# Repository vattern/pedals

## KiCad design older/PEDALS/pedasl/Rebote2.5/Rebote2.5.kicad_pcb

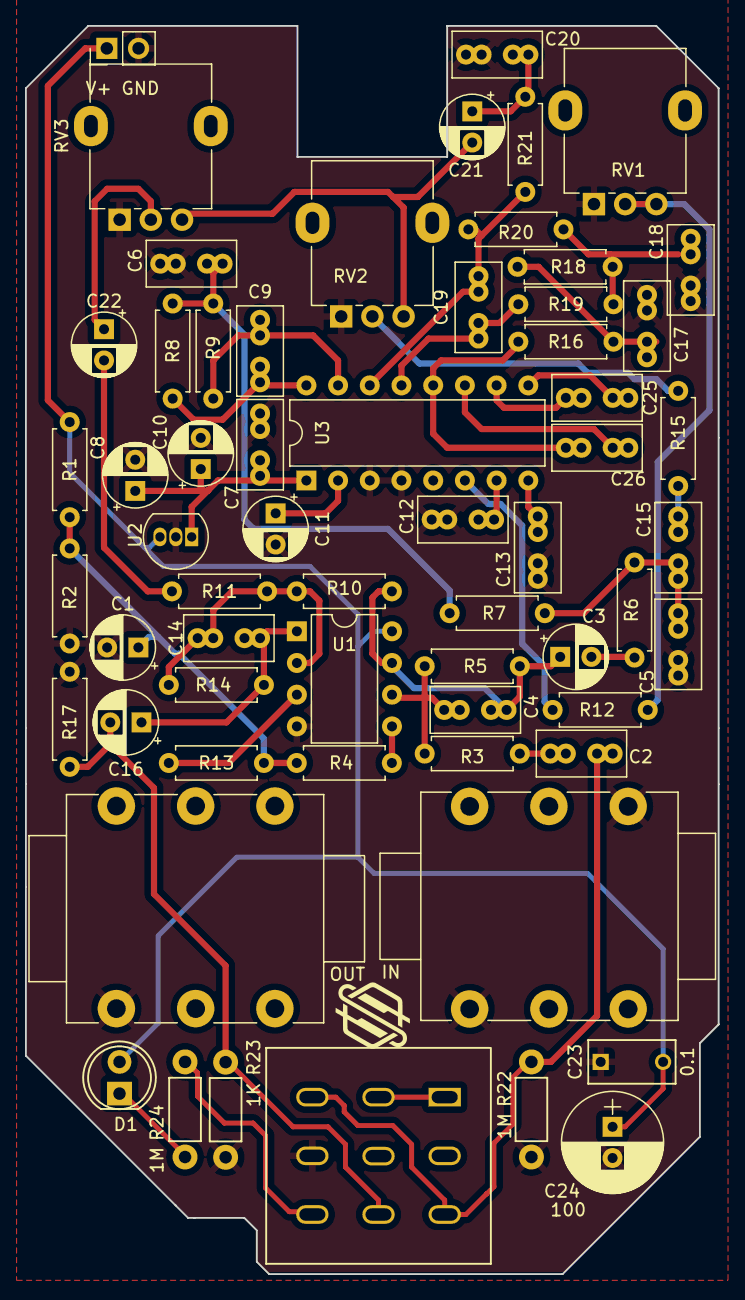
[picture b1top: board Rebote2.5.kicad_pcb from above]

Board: 2 copper layers, 55.5 x 100.0 mm, 62 parts (0 on the bottom side), 40 nets.

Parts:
C1, C8, C10, C11: 47uF; CP_Radial_D5.0mm_P2.50mm
C2: 8n2; C_Rect_L7.0mm_W3.5mm_P2.50mm_P5.00mm
C3, C16, C21, C22: 1uF; CP_Radial_D5.0mm_P2.50mm
C4: 5pF; C_Rect_L7.0mm_W3.5mm_P2.50mm_P5.00mm
C5: 27nF; C_Rect_L7.0mm_W3.5mm_P2.50mm_P5.00mm
C6, C17, C18: 10nF; C_Rect_L7.0mm_W3.5mm_P2.50mm_P5.00mm
C7, C12, C13, C15, C20: 100nF; C_Rect_L7.0mm_W3.5mm_P2.50mm_P5.00mm
C9: 560pF; C_Rect_L7.0mm_W3.5mm_P2.50mm_P5.00mm
C14: 51pF; C_Rect_L7.0mm_W3.5mm_P2.50mm_P5.00mm
C19: 1nF; C_Rect_L7.0mm_W3.5mm_P2.50mm_P5.00mm
C23: 0.1; C_Rect_L7_W3.5_P5
C24: 100; CP_Radial_D8.0mm_P2.50mm
C25, C26: 82nF; C_Rect_L7.0mm_W3.5mm_P2.50mm_P5.00mm
D1: LED; LED-5MM
J1: V+ GND; Pin_Header_Straight_1x02_Pitch2.54mm
J2: IN; NMJ6HCD2
J3: OUT; NMJ6HCD2
N1: Housing; 1590B
R1, R2, R6, R7, R8, R16, R18, R19: 12K; R_Axial_DIN0207_L6.3mm_D2.5mm_P7.62mm_Horizontal
R3, R4, R5: 510K; R_Axial_DIN0207_L6.3mm_D2.5mm_P7.62mm_Horizontal
R9: 47K; R_Axial_DIN0207_L6.3mm_D2.5mm_P7.62mm_Horizontal
R10, R14, R20: 24K; R_Axial_DIN0207_L6.3mm_D2.5mm_P7.62mm_Horizontal
R11: 33K; R_Axial_DIN0207_L6.3mm_D2.5mm_P7.62mm_Horizontal
R12, R13: 1k; R_Axial_DIN0207_L6.3mm_D2.5mm_P7.62mm_Horizontal
R15: 15K; R_Axial_DIN0207_L6.3mm_D2.5mm_P7.62mm_Horizontal
R17: 100K; R_Axial_DIN0207_L6.3mm_D2.5mm_P7.62mm_Horizontal
R21: 2k7; R_Axial_DIN0207_L6.3mm_D2.5mm_P7.62mm_Horizontal
R22, R24: 1M; Resistor_Horizontal_RM7mm
R23: 1K; Resistor_Horizontal_RM7mm
RV1: 50KB; Potentiometer_Alpha_RD901F-40-00D_Single_Vertical
RV2: 25KB; Potentiometer_Alpha_RD901F-40-00D_Single_Vertical
RV3: 100KB; Potentiometer_Alpha_RD901F-40-00D_Single_Vertical
SW1: SW_3PDT; 3PDT-Footswitch
U1: TL072; DIP-8_W7.62mm
U2: L78L05_TO92; TO-92_Inline
U3: PT2399; DIP-16_W7.62mm

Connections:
+5V: C7.2, C8.1, C10.1, U2.1 (VO), U3.1 (VCC)
+9V: C23.2, C24.1, D1.2 (A), J1.1, R1.1, U1.8 (V+), U2.3 (VI)
AI: C3.1, C4.2, R5.2, R10.1, U1.7
DELAY_OUT: C26.2, R16.1, U3.12 (OP2-OUT)
GND: C1.2, C5.1, C6.1, C7.1, C8.2, C10.2, C11.2, C12.1, C13.1, C17.1, C18.1, C20.1, C23.1, C24.2, J1.2, J2.1 (S), J2.5 (TN), J3.1 (S), R2.2, R17.1, R22.2, R23.2, RV1.1, RV2.1, RV3.1, SW1.6 (B), U1.4 (V-), U2.2 (GND), U3.3 (AGND), U3.4 (DGND)
I: C2.1, R22.1, SW1.3 (A), SW1.7 (C)
LPF1-IN: C9.1, R8.2, U3.16 (LPF1-IN)
LPF1-OUT: C9.2, R9.2, U3.15 (LPF1-OUT)
LPF2-IN: C19.1, R19.2, U3.13 (LPF2-IN)
LPF2-OUT: C19.2, R20.2, R21.1, U3.14 (LPF2-OUT)
unnamed: C2.2, R3.1
unnamed: C3.2, R6.1
unnamed: C6.2, R7.2, R8.1, R9.1
unnamed: C14.2, C16.1, R14.2, U1.1
unnamed: C5.2, C15.1, R6.2, R7.1
unnamed: C15.2, R15.1
unnamed: C17.2, R16.2, R18.1
unnamed: C18.2, R18.2, R19.1, R20.1
unnamed: C20.2, C21.1, R21.2
unnamed: C21.2, RV2.3, RV3.3
unnamed: C22.1, RV3.2
unnamed: C22.2, R11.1
unnamed: D1.1 (K), R24.1
unnamed: R12.2, RV1.2, RV1.3
unnamed: R15.2, RV2.2
unnamed: SW1.1 (A), SW1.2 (A)
unnamed: R24.2, SW1.9 (C)
unnamed: R13.2, U1.3 (+)
unnamed: C14.1, R10.2, R11.2, R14.1, U1.2 (-)
unnamed: R4.2, U1.5 (+)
unnamed: C4.1, R3.2, R5.1, U1.6 (-)
unnamed: C13.2, U3.8 (CC0)
unnamed: C12.2, U3.7 (CC1)
unnamed: C25.2, U3.10 (OP1-IN)
unnamed: C25.1, U3.9 (OP1-OUT)
unnamed: C26.1, U3.11 (OP2-IN)
unnamed: C11.1, U3.2 (REF)
unnamed: R12.1, U3.6 (VCO)
O: C16.2, R17.2, R23.1, SW1.8 (C)
VD: C1.1, R1.2, R2.1, R4.1, R13.1

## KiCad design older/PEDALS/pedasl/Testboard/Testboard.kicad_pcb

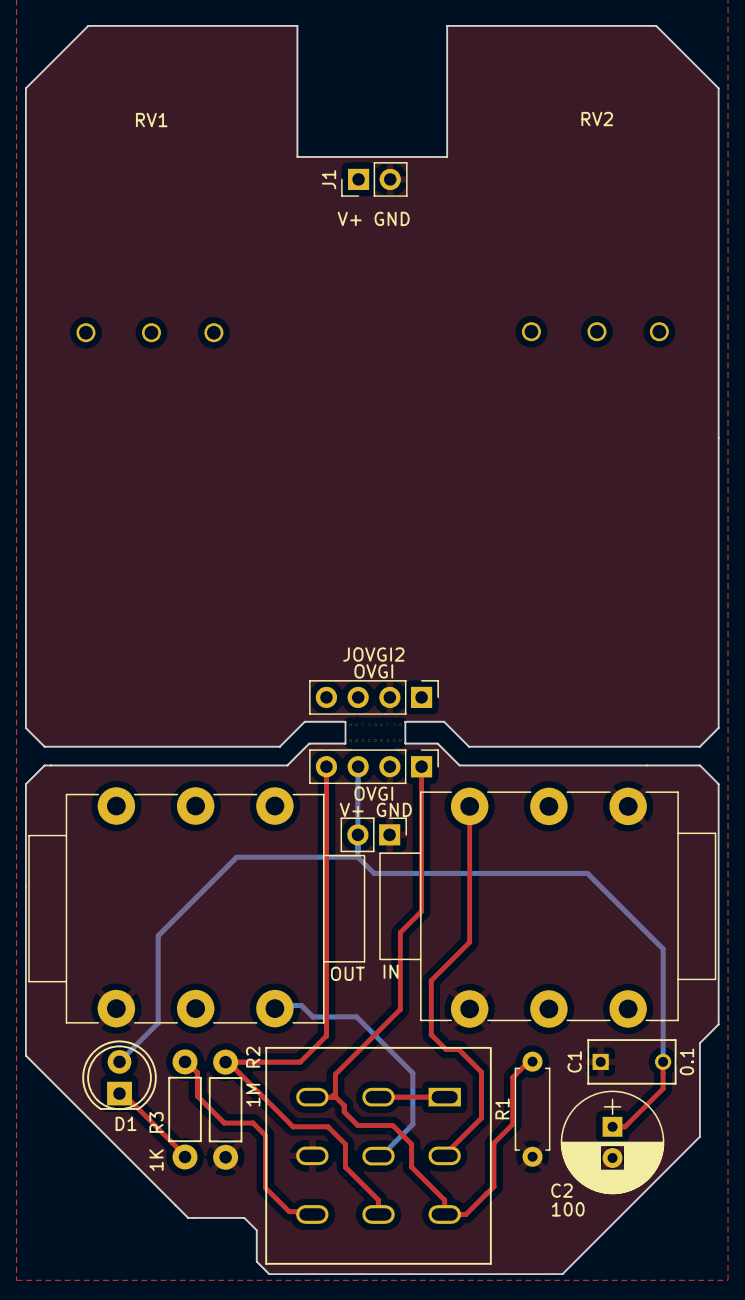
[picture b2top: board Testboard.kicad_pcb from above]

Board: 2 copper layers, 55.5 x 100.0 mm, 15 parts (0 on the bottom side), 9 nets.

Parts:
C1: 0.1; C_Rect_L7_W3.5_P5
C2: 100; CP_Radial_D8.0mm_P2.50mm
D1: LED; LED-5MM
J1, J4: V+ GND; Pin_Header_Straight_1x02_Pitch2.54mm
J2: IN; NMJ6HCD2
J3: OUT; NMJ6HCD2
JOVGI1, JOVGI2: OVGI; Pin_Header_Straight_1x04_Pitch2.54mm
R1: R; R_Axial_DIN0207_L6.3mm_D2.5mm_P7.62mm_Horizontal
R2: 1M; Resistor_Horizontal_RM7mm
R3: 1K; Resistor_Horizontal_RM7mm
RV1, RV2: R_Potentiometer; Potentiometer_ALPHA_RV16106N
SW1: SW_3PDT; 3PDT-Footswitch

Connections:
+9V: C1.2, C2.1, D1.2, J1.1, J4.2, JOVGI1.3, JOVGI2.3
/I: JOVGI1.1, JOVGI2.1, SW1.3, SW1.7
/O: JOVGI1.4, JOVGI2.4, R2.1, SW1.8
GND: C1.1, C2.2, J1.2, J2.1, J2.5, J3.1, J4.1, JOVGI1.2, JOVGI2.2, R1.1, R2.2, SW1.6
unnamed: D1.1, R3.1
unnamed: J2.2, SW1.4
unnamed: J3.2, SW1.5
unnamed: R3.2, SW1.9
unnamed: SW1.1, SW1.2

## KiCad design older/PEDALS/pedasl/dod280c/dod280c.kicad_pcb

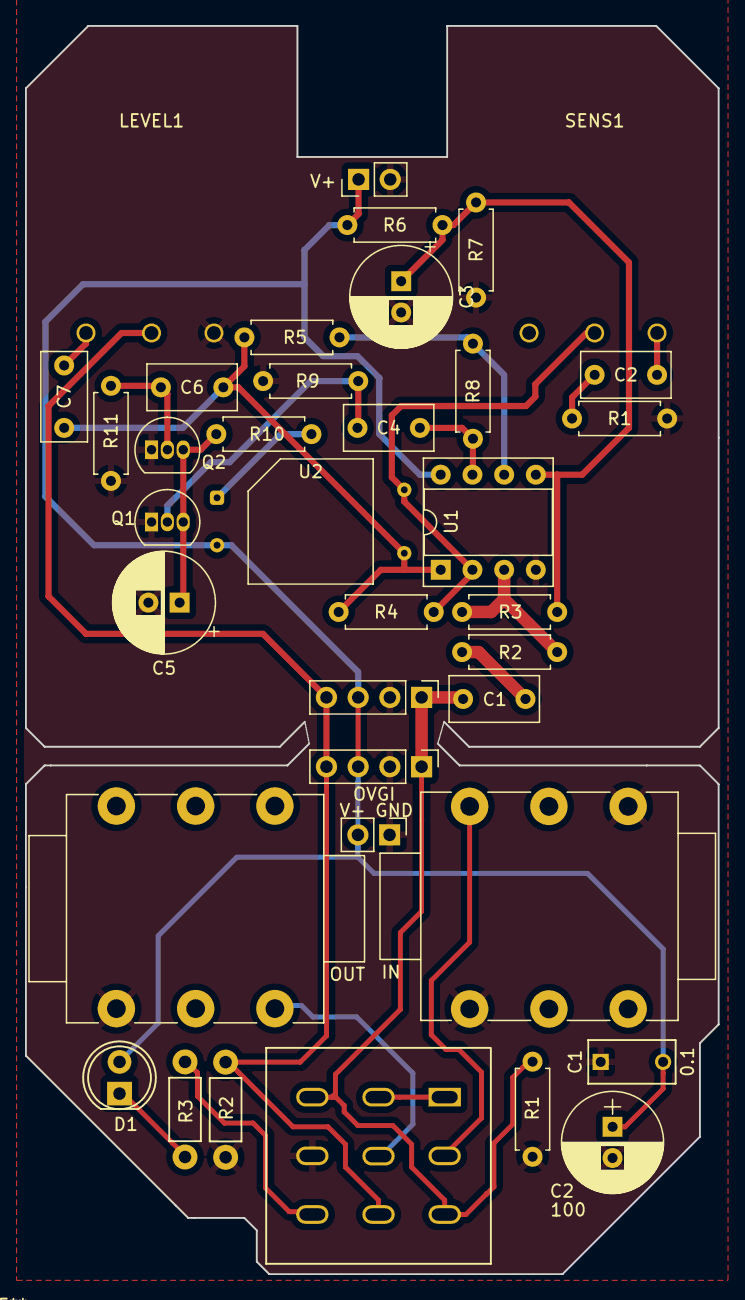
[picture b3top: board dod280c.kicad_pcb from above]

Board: 2 copper layers, 55.5 x 100.0 mm, 37 parts (0 on the bottom side), 23 nets.

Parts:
C1: 10nF; C_Rect_L7.0mm_W3.5mm_P5.00mm
C1#2: 0.1; C_Rect_L7_W3.5_P5
C2, C4, C6, C7: 50nF; C_Rect_L7.0mm_W3.5mm_P5.00mm
C2#2: 100; CP_Radial_D8.0mm_P2.50mm
C3: 10uF; CP_Radial_D8.0mm_P2.50mm
C5: 47uF; CP_Radial_D8.0mm_P2.50mm
D1: LED; LED-5MM
J1: V+; Pin_Header_Straight_1x02_Pitch2.54mm
J2: IN; NMJ6HCD2
J3: OUT; NMJ6HCD2
J4: V+ GND; Pin_Header_Straight_1x02_Pitch2.54mm
JOVGI1, JOVGI2: OVGI; Pin_Header_Straight_1x04_Pitch2.54mm
LEVEL1: 100KA; Potentiometer_ALPHA_RV16106N
Q1, Q2: 2N3904; TO-92_Inline
R1: R; R_Axial_DIN0207_L6.3mm_D2.5mm_P7.62mm_Horizontal
R1#2, R6, R7: 22K; R_Axial_DIN0207_L6.3mm_D2.5mm_P7.62mm_Horizontal
R2: 1M; Resistor_Horizontal_RM7mm
R2#2: 10K; R_Axial_DIN0207_L6.3mm_D2.5mm_P7.62mm_Horizontal
R3: 1K; Resistor_Horizontal_RM7mm
R3#2: 470K; R_Axial_DIN0207_L6.3mm_D2.5mm_P7.62mm_Horizontal
R4: 1M; R_Axial_DIN0207_L6.3mm_D2.5mm_P7.62mm_Horizontal
R5, R8: 100K; R_Axial_DIN0207_L6.3mm_D2.5mm_P7.62mm_Horizontal
R9, R11: 220K; R_Axial_DIN0207_L6.3mm_D2.5mm_P7.62mm_Horizontal
R10: 4K7; R_Axial_DIN0207_L6.3mm_D2.5mm_P7.62mm_Horizontal
SENS1: 500KB; Potentiometer_ALPHA_RV16106N
SW1: SW_3PDT; 3PDT-Footswitch
U1: LM358; DIP-8_W7.62mm_Socket
U2: VTL5C; PerkinElmer_VTL5C

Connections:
+9V: C1#2.2, C2#2.1, D1.2, J1.1, J4.2, JOVGI1.3, JOVGI2.3, R6.1, U1.8 (V+), U2.2 (+)
GND: C1#2.1, C2#2.2, C3.2, C5.2, J1.2, J2.1, J2.5, J3.1, J4.1, JOVGI1.2, JOVGI2.2, LEVEL1.3, Q1.1 (E), Q2.1 (E), R1.1, R1#2.2, R2.2, R7.2, R9.2, R11.2, SW1.6, U1.4 (V-)
unnamed: C1.2, R2#2.1
unnamed: C2.1, R1#2.1
unnamed: C2.2, SENS1.3
unnamed: C4.1, R8.2, U1.7
unnamed: C6.2, C7.1, R4.2, R5.1, U1.1, U2.4
unnamed: C7.2, LEVEL1.1
unnamed: D1.1, R3.1
unnamed: J2.2, SW1.4
unnamed: J3.2, SW1.5
unnamed: C4.2, Q1.2 (B), R9.1
unnamed: C5.1, Q1.3 (C), Q2.3 (C), R10.2
unnamed: C6.1, Q2.2 (B), R11.1
unnamed: R3.2, SW1.9
unnamed: SW1.1, SW1.2
unnamed: R2#2.2, R3#2.2, U1.3 (+)
unnamed: R4.1, SENS1.2, U1.2 (-), U2.3
unnamed: R5.2, R8.1, U1.6 (-)
unnamed: R10.1, U2.1 (-)
VB: C3.1, R3#2.1, R6.2, R7.1, U1.5 (+)
/I: C1.1, JOVGI1.1, JOVGI2.1, R1.2, SW1.3, SW1.7
/O: JOVGI1.4, JOVGI2.4, LEVEL1.2, R2.1, SW1.8

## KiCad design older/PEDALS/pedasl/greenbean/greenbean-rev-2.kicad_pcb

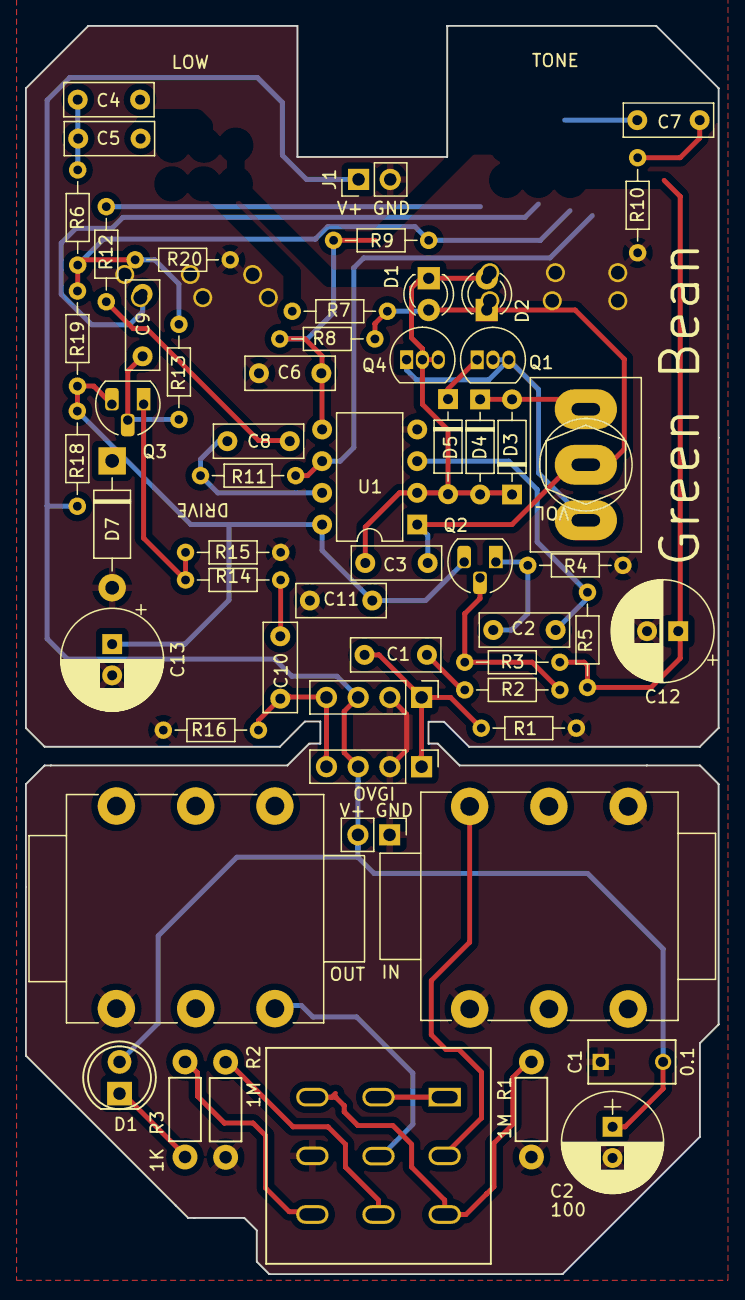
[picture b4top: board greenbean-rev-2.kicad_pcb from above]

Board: 2 copper layers, 55.5 x 100.0 mm, 61 parts (0 on the bottom side), 36 nets.

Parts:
C1: 0.1; C_Rect_L7_W3.5_P5
C1#2: 20n; C_Disc_D7.0mm_W2.5mm_P5.00mm
C2, C8, C10: 1u; C_Disc_D7.0mm_W2.5mm_P5.00mm
C2#2: 100; CP_Radial_D8.0mm_P2.50mm
C3: 51p; C_Disc_D7.0mm_W2.5mm_P5.00mm
C4: 47n; C_Disc_D7.0mm_W2.5mm_P5.00mm
C5: 150n; C_Disc_D7.0mm_W2.5mm_P5.00mm
C6, C7, C11: 220n; C_Disc_D7.0mm_W2.5mm_P5.00mm
C9: 100n; C_Disc_D7.0mm_W2.5mm_P5.00mm
C12, C13: C_Polarized; CP_Radial_D8.0mm_P2.50mm
D1, D2: LED; LED_D3.0mm
D1#2: LED; LED-5MM
D3, D4: 1N914; D_DO-35_SOD27_P7.62mm_Horizontal
D5: BAT41; D_DO-35_SOD27_P7.62mm_Horizontal
D7: 1N4001; D_DO-41_SOD81_P10.16mm_Horizontal
DRIVE: 500KA; Potentiometer_ALPHA_RV16106N
J1, J4: V+ GND; Pin_Header_Straight_1x02_Pitch2.54mm
J2: IN; NMJ6HCD2
J3: OUT; NMJ6HCD2
JOVGI1, JOVGI2: OVGI; Pin_Header_Straight_1x04_Pitch2.54mm
LOW: 20KB; Potentiometer_ALPHA_RV16106N
Q1, Q4: 2N7000; TO-92_Inline
Q2, Q3: Q_NPN_EBC; TO-92L_HandSolder
R1: 1M; R_Axial_DIN0204_L3.6mm_D1.6mm_P7.62mm_Horizontal
R1#2, R2#2: 1M; Resistor_Horizontal_RM7mm
R2, R8, R11, R12: 1k; R_Axial_DIN0204_L3.6mm_D1.6mm_P7.62mm_Horizontal
R3, R13: 510k; R_Axial_DIN0204_L3.6mm_D1.6mm_P7.62mm_Horizontal
R3#2: 1K; Resistor_Horizontal_RM7mm
R4, R5, R9, R14, R16, R19, R20: 10k; R_Axial_DIN0204_L3.6mm_D1.6mm_P7.62mm_Horizontal
R6: 4k7; R_Axial_DIN0204_L3.6mm_D1.6mm_P7.62mm_Horizontal
R7: 51k; R_Axial_DIN0204_L3.6mm_D1.6mm_P7.62mm_Horizontal
R10: 220R; R_Axial_DIN0204_L3.6mm_D1.6mm_P7.62mm_Horizontal
R15: 100R; R_Axial_DIN0204_L3.6mm_D1.6mm_P7.62mm_Horizontal
R18: 47R; R_Axial_DIN0204_L3.6mm_D1.6mm_P7.62mm_Horizontal
SW1: SW_3PDT; 3PDT-Footswitch
SW1#2: SW_SPDT; SW_Toggle_Blue_wSlots
TONE: 20KB; Potentiometer_ALPHA_RV16106N
U1: RC4558; DIP-8_W7.62mm
VOL: 100KB; Potentiometer_ALPHA_RV16106N

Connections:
+9V: C1.2, C2#2.1, D1#2.2, J1.1, J4.2, JOVGI1.3, JOVGI2.3, R18.2
/I: R1#2.1, SW1.3, SW1.7
/O: R2#2.1, SW1.8
A: C3.1, C4.2, D1.1 (K), D2.2 (A), D3.1 (K), D4.2 (A), D5.2 (A), DRIVE.1, LOW.3, Q4.2 (G), Q4.3 (D), U1.2 (-)
B: C3.2, D1.2 (A), D2.1 (K), R7.2, R8.1, SW1#2.2 (B), U1.1
GND: C1.1, C2#2.2, C6.1, C11.1, C12.2, C13.2, D7.2 (A), J1.2, J2.1, J2.5, J3.1, J4.1, JOVGI1.2, JOVGI2.2, R1.1, R1#2.2, R2#2.2, R4.1, R10.1, R14.1, R16.1, R20.1, SW1.6, U1.4 (V-)
unnamed: C1#2.2, R2.2
unnamed: C4.1, C5.1, R6.2
unnamed: C5.2, LOW.2
unnamed: C7.1, R10.2
unnamed: C7.2, TONE.2
unnamed: C8.1, R11.2, U1.7
unnamed: C8.2, R12.1
unnamed: C9.1, VOL.2
unnamed: C10.1, R15.2
unnamed: D1#2.1, R3#2.1
unnamed: D3.2 (A), D4.1 (K), SW1#2.1 (A)
unnamed: D5.1 (K), Q1.1 (S)
unnamed: DRIVE.2, DRIVE.3, R7.1
unnamed: J2.2, SW1.4
unnamed: J3.2, SW1.5
unnamed: Q1.2 (G), Q1.3 (D), Q4.1 (S), SW1#2.3 (C)
unnamed: Q2.2 (B), R2.1, R3.1
unnamed: C2.1, Q2.1 (E), R4.2
unnamed: C9.2, Q3.2 (B), R13.1
unnamed: Q3.1 (E), R14.2, R15.1
unnamed: R3#2.2, SW1.9
unnamed: R12.2, VOL.3
unnamed: SW1.1, SW1.2
unnamed: C2.2, R5.1, U1.3 (+)
unnamed: C6.2, R8.2, R9.1, TONE.1, U1.5 (+)
unnamed: R11.1, TONE.3, U1.6 (-)
VB: C12.1, R3.2, R5.2, R6.1, R9.2, R13.2, R19.1, R20.2, VOL.1
VC: C11.2, C13.1, D7.1 (K), Q2.3 (C), Q3.3 (C), R18.1, R19.2, U1.8 (V+)
/I: C1#2.1, JOVGI1.1, JOVGI2.1, R1.2
/O: C10.2, JOVGI1.4, JOVGI2.4, R16.2

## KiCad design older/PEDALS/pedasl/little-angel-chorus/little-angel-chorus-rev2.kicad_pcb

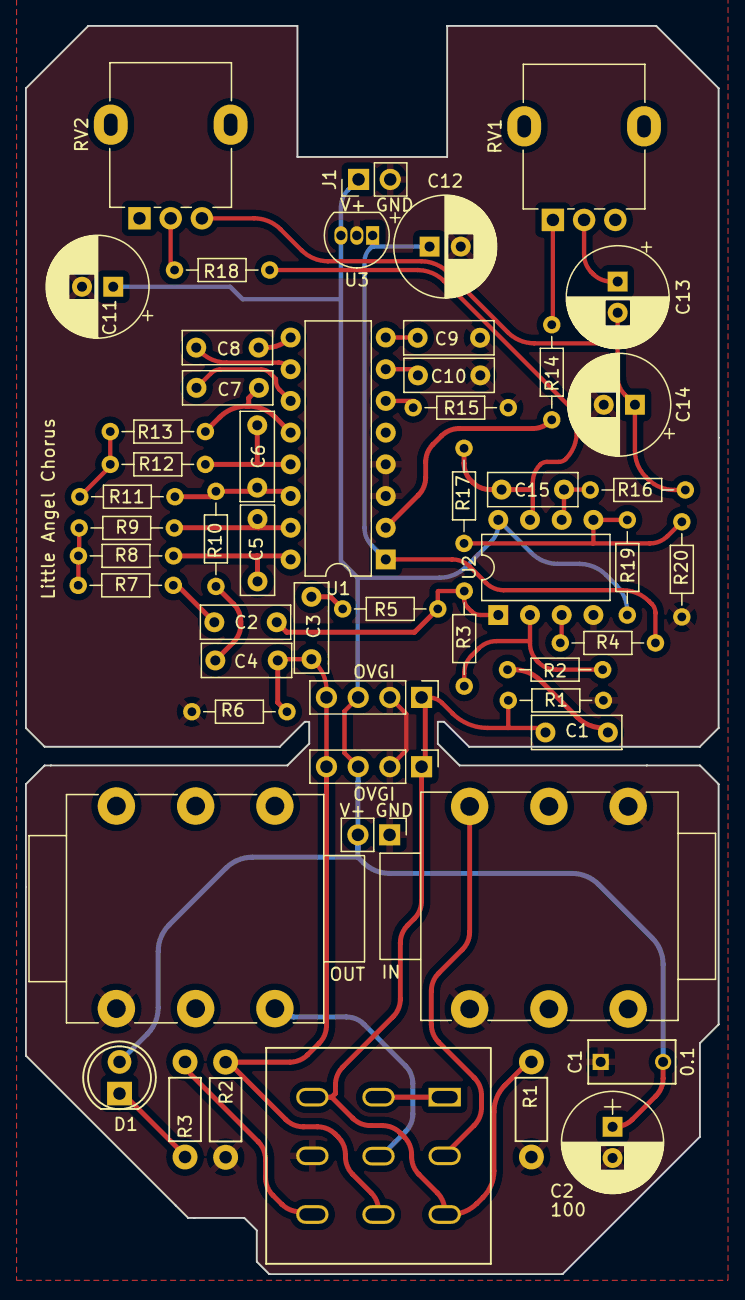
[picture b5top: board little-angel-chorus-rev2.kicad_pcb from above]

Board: 2 copper layers, 55.5 x 100.0 mm, 53 parts (0 on the bottom side), 38 nets.

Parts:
C1: 0.1; C_Rect_L7_W3.5_P5
C1#2, C2, C3, C4, C9, C10: 100nF; C_Disc_D7.0mm_W2.5mm_P5.00mm
C2#2: 100; CP_Radial_D8.0mm_P2.50mm
C5, C6: 1nF; C_Disc_D7.0mm_W2.5mm_P5.00mm
C7, C8, C15: 10nF; C_Disc_D7.0mm_W2.5mm_P5.00mm
C11: 100uF; CP_Radial_D8.0mm_P2.50mm
C12: 47uF; CP_Radial_D8.0mm_P2.50mm
C13, C14: 10uF; CP_Radial_D8.0mm_P2.50mm
D1: LED; LED-5MM
J1, J4: V+ GND; Pin_Header_Straight_1x02_Pitch2.54mm
J2: IN; NMJ6HCD2
J3: OUT; NMJ6HCD2
JOVGI1, JOVGI2: OVGI; Pin_Header_Straight_1x04_Pitch2.54mm
R1, R2: 1M; Resistor_Horizontal_RM7mm
R1#2, R3: 1M; R_Axial_DIN0204_L3.6mm_D1.6mm_P7.62mm_Horizontal
R2#2: 470k; R_Axial_DIN0204_L3.6mm_D1.6mm_P7.62mm_Horizontal
R3#2: 1K; Resistor_Horizontal_RM7mm
R4: 330k; R_Axial_DIN0204_L3.6mm_D1.6mm_P7.62mm_Horizontal
R5, R7, R8, R9, R10, R11, R12, R13: 10k; R_Axial_DIN0204_L3.6mm_D1.6mm_P7.62mm_Horizontal
R6, R19: 100k; R_Axial_DIN0204_L3.6mm_D1.6mm_P7.62mm_Horizontal
R14: 33k; R_Axial_DIN0204_L3.6mm_D1.6mm_P7.62mm_Horizontal
R15: 100R; R_Axial_DIN0204_L3.6mm_D1.6mm_P7.62mm_Horizontal
R16: 220K; R_Axial_DIN0204_L3.6mm_D1.6mm_P7.62mm_Horizontal
R17: 220k; R_Axial_DIN0204_L3.6mm_D1.6mm_P7.62mm_Horizontal
R18: 4k7; R_Axial_DIN0204_L3.6mm_D1.6mm_P7.62mm_Horizontal
R20: 47k; R_Axial_DIN0204_L3.6mm_D1.6mm_P7.62mm_Horizontal
RV1: 470K lin; Potentiometer_Alpha_RD901F-40-00D_Single_Vertical
RV2: 100k lin; Potentiometer_Alpha_RD901F-40-00D_Single_Vertical
SW1: SW_3PDT; 3PDT-Footswitch
U1: PT2399; DIP-16_W7.62mm
U2: NE5532; DIP-8_W7.62mm
U3: L78L05_TO92; TO-92_Inline

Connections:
+9V: C1.2, C2#2.1, C11.1, D1.2, J1.1, J4.2, JOVGI1.3, JOVGI2.3, R19.2, U2.8 (V+), U3.3 (VI)
GND: C1.1, C2#2.2, C9.1, C10.1, C11.2, C12.2, C14.2, J1.2, J2.1, J2.5, J3.1, J4.1, JOVGI1.2, JOVGI2.2, R1.2, R1#2.2, R2.2, R6.1, R15.1, R20.1, SW1.6, U1.3 (AGND), U1.4 (DGND), U2.4 (V-), U3.2 (GND)
unnamed: C1#2.2, R2#2.1
unnamed: C2.1, R7.1
unnamed: C2.2, R3.2, R5.1, U2.1
unnamed: C3.1, R5.2
unnamed: C4.1, R10.2
unnamed: C13.1, RV1.2
unnamed: C13.2, C14.1, R16.2, RV2.3
unnamed: C15.2, R17.2, R18.1, U2.7
unnamed: D1.1, R3#2.1
unnamed: J2.2, SW1.4
unnamed: J3.2, SW1.5
unnamed: R3#2.2, SW1.9
unnamed: R7.2, R8.2, R9.2
unnamed: R11.1, R12.1, R13.1
unnamed: R14.1, RV1.1
unnamed: R18.2, RV2.2
unnamed: SW1.1, SW1.2
unnamed: C9.2, U1.8 (CC0)
unnamed: C10.2, U1.7 (CC1)
unnamed: C5.1, R8.1, U1.16 (LPF1-IN)
unnamed: C5.2, R9.1, U1.15 (LPF1-OUT)
unnamed: C6.2, R12.2, U1.13 (LPF2-IN)
unnamed: C6.1, R10.1, R11.2, U1.14 (LPF2-OUT)
unnamed: C8.1, U1.10 (OP1-IN)
unnamed: C8.2, U1.9 (OP1-OUT)
unnamed: C7.2, U1.11 (OP2-IN)
unnamed: C7.1, R13.2, U1.12 (OP2-OUT)
unnamed: R14.2, U1.2 (REF)
unnamed: C12.1, R4.1, U1.1 (VCC), U3.1 (VO)
unnamed: R15.2, U1.6 (VCO)
unnamed: R4.2, U2.3 (+)
unnamed: R2#2.2, R3.1, U2.2 (-)
unnamed: R17.1, R19.1, R20.2, U2.5 (+)
unnamed: C15.1, R16.1, U2.6 (-)
/I: C1#2.1, JOVGI1.1, JOVGI2.1, R1.1, R1#2.1, SW1.3, SW1.7
/O: C3.2, C4.2, JOVGI1.4, JOVGI2.4, R2.1, R6.2, SW1.8

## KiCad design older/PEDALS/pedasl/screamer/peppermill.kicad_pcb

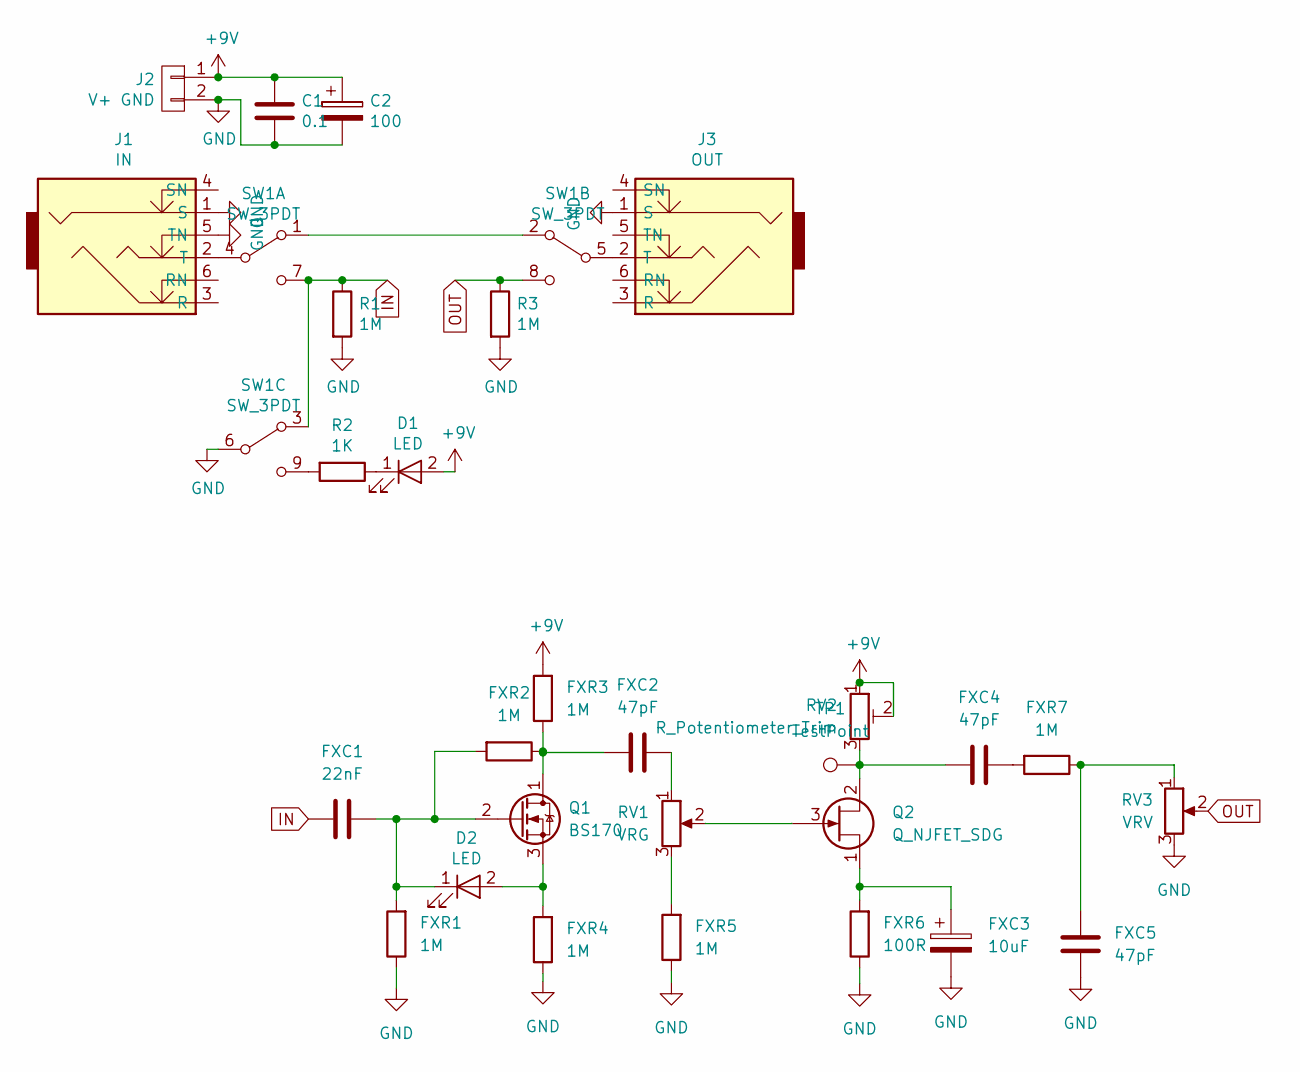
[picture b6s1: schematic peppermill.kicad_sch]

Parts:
C1: 0.1; C_Rect_L7_W3.5_P5
C2: 100; CP_Radial_D8.0mm_P2.50mm
D1: LED; LED-5MM
D2: LED; LED_D5.0mm
FXC1: 22nF; C_Disc_D5.0mm_W2.5mm_P5.00mm
FXC2, FXC4, FXC5: 47pF; C_Disc_D5.0mm_W2.5mm_P5.00mm
FXC3: 10uF; CP_Radial_D7.5mm_P2.50mm
FXR1, FXR2, FXR3, FXR4, FXR5, FXR7: 1M; R_Axial_DIN0207_L6.3mm_D2.5mm_P7.62mm_Horizontal
FXR6: 100R; R_Axial_DIN0207_L6.3mm_D2.5mm_P7.62mm_Horizontal
J1: IN; NMJ6HCD2
J2: V+ GND; Pin_Header_Straight_1x02_Pitch2.54mm
J3: OUT; NMJ6HCD2
Q1: BS170; TO-92_Inline
Q2: Q_NJFET_SDG; TO-92L_Inline_Wide
R1, R3: 1M; Resistor_Horizontal_RM7mm
R2: 1K; Resistor_Horizontal_RM7mm
RV1: VRG; Potentiometer_Alps_RK09K_Single_Vertical
RV2: R_Potentiometer_Trim; Potentiometer_TT_P0915N
RV3: VRV; Potentiometer_Alps_RK09K_Single_Vertical
SW1: SW_3PDT; 3PDT-Footswitch
TP1: TestPoint; TestPoint_Loop_D2.50mm_Drill1.85mm

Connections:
+9V: C1.2, C2.1, D1.2 (A), FXR3.2, J2.1, RV2.1, RV2.2
GND: C1.1, C2.2, FXC3.2, FXC5.1, FXR1.1, FXR4.1, FXR5.1, FXR6.1, J1.1 (S), J1.5 (TN), J2.2, J3.1 (S), R1.2, R3.2, RV3.3, SW1.6 (B)
IN: FXC1.1, R1.1, SW1.3 (A), SW1.7 (C)
unnamed: D1.1 (K), R2.1
unnamed: D2.1 (K), FXC1.2, FXR1.2, FXR2.2, Q1.2 (G)
unnamed: D2.2 (A), FXR4.2, Q1.3 (S)
unnamed: FXC2.1, FXR2.1, FXR3.1, Q1.1 (D)
unnamed: FXC2.2, RV1.1
unnamed: FXC3.1, FXR6.2, Q2.1 (S)
unnamed: FXC4.1, Q2.2 (D), RV2.3, TP1.1
unnamed: FXC4.2, FXR7.2
unnamed: FXC5.2, FXR7.1, RV3.1
unnamed: FXR5.2, RV1.3
unnamed: J1.2 (T), SW1.4 (B)
unnamed: J3.2 (T), SW1.5 (B)
unnamed: Q2.3 (G), RV1.2
unnamed: R2.2, SW1.9 (C)
unnamed: SW1.1 (A), SW1.2 (A)
OUT: R3.1, RV3.2, SW1.8 (C)

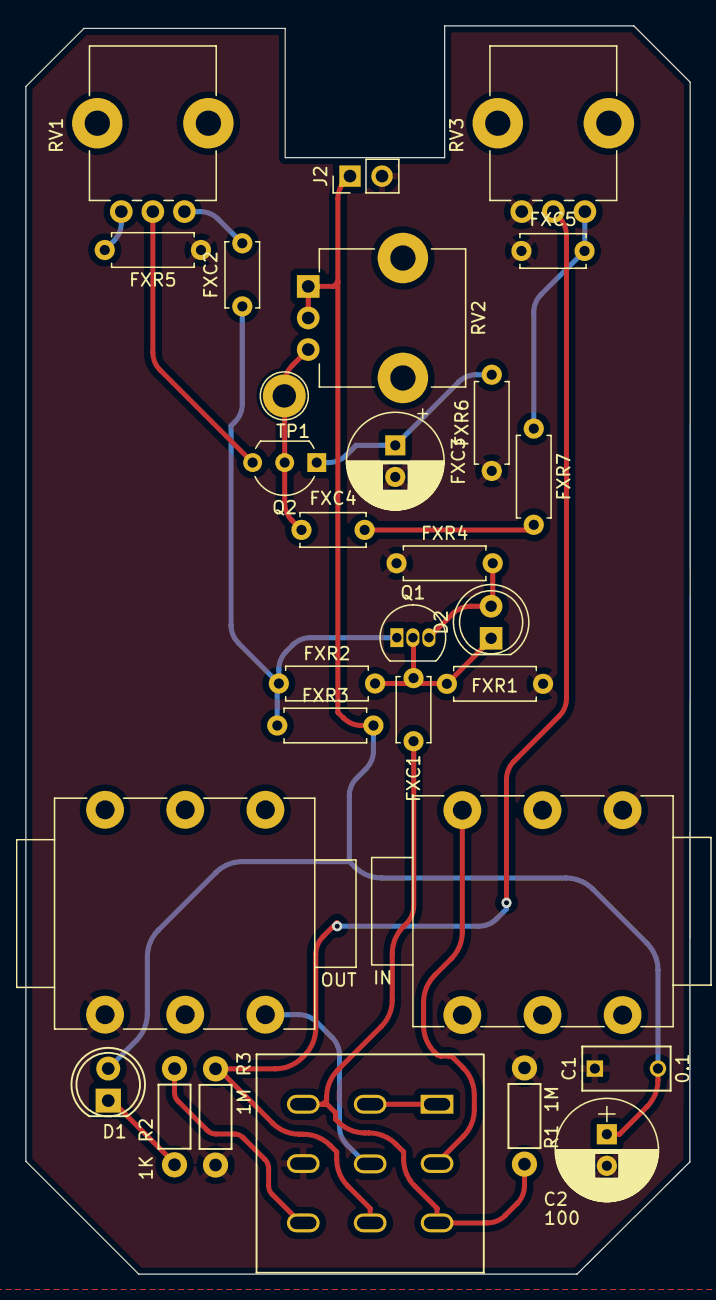
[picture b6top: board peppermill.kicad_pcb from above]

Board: 2 copper layers, 52.6 x 98.9 mm, 29 parts (0 on the bottom side), 19 nets.

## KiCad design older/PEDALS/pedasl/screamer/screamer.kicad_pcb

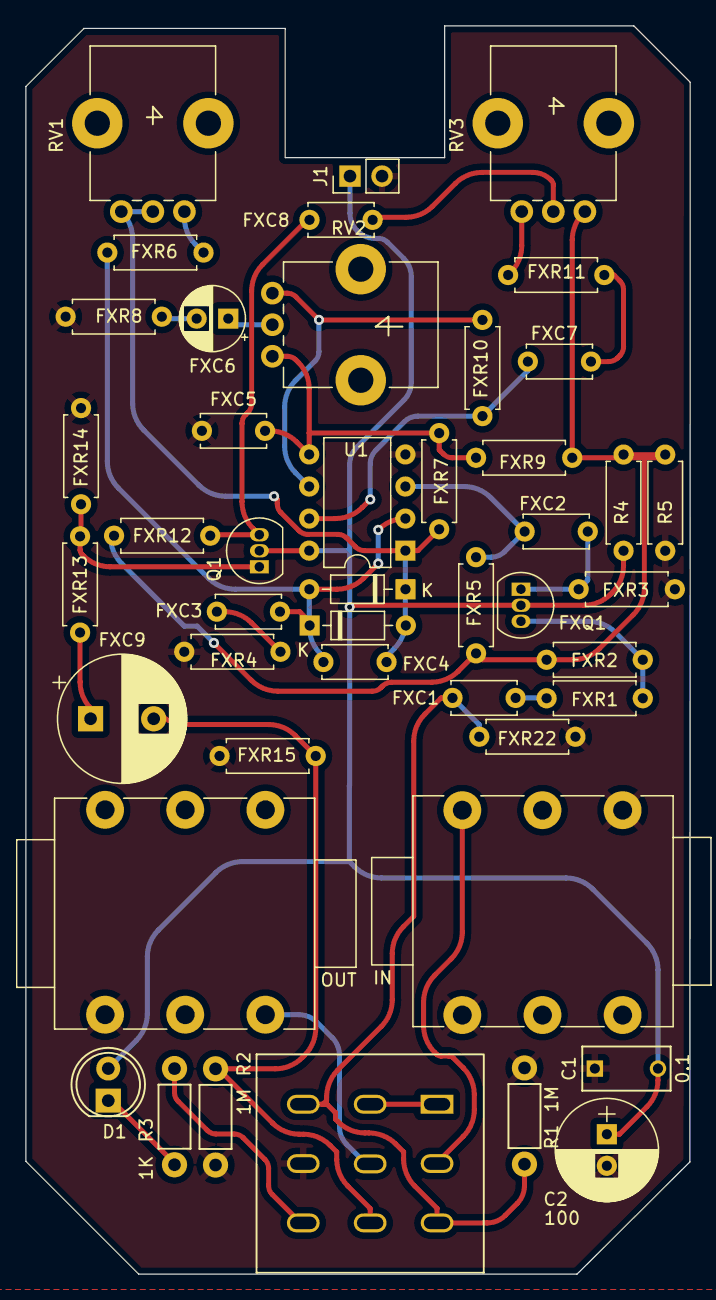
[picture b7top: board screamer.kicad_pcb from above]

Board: 2 copper layers, 52.6 x 98.9 mm, 45 parts (0 on the bottom side), 29 nets.

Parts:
C1: 0.1; C_Rect_L7_W3.5_P5
C2: 100; CP_Radial_D8.0mm_P2.50mm
D1: LED; LED-5MM
FXC1: 22nF; C_Disc_D5.0mm_W2.5mm_P5.00mm
FXC2, FXC7: 1uF NP; C_Disc_D5.0mm_W2.5mm_P5.00mm
FXC3: 47nF; C_Disc_D5.0mm_W2.5mm_P5.00mm
FXC4: 47pF; C_Disc_D5.0mm_W2.5mm_P5.00mm
FXC5: C; C_Disc_D5.0mm_W2.5mm_P5.00mm
FXC6: .22uF tant; CP_Radial_D5.0mm_P2.50mm
FXC8: 100nF; C_Disc_D5.0mm_W2.5mm_P5.00mm
FXC9: 10uF; CP_Radial_D10.0mm_P5.00mm
FXD1, FXD2: 1N914; D_DO-35_SOD27_P7.62mm_Horizontal
FXQ1: 2SC1815; TO-92_Inline
FXR1, FXR7, FXR8, FXR10, FXR11: 1K0; R_Axial_DIN0207_L6.3mm_D2.5mm_P7.62mm_Horizontal
FXR2, FXR12: 510K; R_Axial_DIN0207_L6.3mm_D2.5mm_P7.62mm_Horizontal
FXR3, FXR5, FXR9, FXR13, FXR14: 10K; R_Axial_DIN0207_L6.3mm_D2.5mm_P7.62mm_Horizontal
FXR4: FXR4; R_Axial_DIN0207_L6.3mm_D2.5mm_P7.62mm_Horizontal
FXR6: 51K; R_Axial_DIN0207_L6.3mm_D2.5mm_P7.62mm_Horizontal
FXR15: 100R; R_Axial_DIN0207_L6.3mm_D2.5mm_P7.62mm_Horizontal
FXR22: 1M; R_Axial_DIN0207_L6.3mm_D2.5mm_P7.62mm_Horizontal
J1: V+ GND; Pin_Header_Straight_1x02_Pitch2.54mm
J2: IN; NMJ6HCD2
J3: OUT; NMJ6HCD2
Q1: 2SC1815; TO-92_Inline
R1, R2: 1M; Resistor_Horizontal_RM7mm
R3: 1K; Resistor_Horizontal_RM7mm
R4: PXR1; R_Axial_DIN0207_L6.3mm_D2.5mm_P7.62mm_Horizontal
R5: PXR2; R_Axial_DIN0207_L6.3mm_D2.5mm_P7.62mm_Horizontal
RV1: VRG; Potentiometer_Bourns_PTV09A-1_Single_Vertical
RV2: VRT; Potentiometer_Bourns_PTV09A-1_Single_Vertical
RV3: VRV; Potentiometer_Bourns_PTV09A-1_Single_Vertical
SW1: SW_3PDT; 3PDT-Footswitch
U1: RC4558; DIP-8_W7.62mm

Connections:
+9V: C1.2, C2.1, D1.2 (A), FXQ1.2 (C), J1.1, Q1.2 (C), R4.1, U1.8 (V+)
+BATT: FXR2.1, FXR5.1, FXR9.1, FXR12.1, R4.2, R5.1, RV3.1
GND: C1.1, C2.2, FXC5.1, FXR3.1, FXR4.2, FXR8.1, FXR14.1, FXR15.1, FXR22.1, J1.2, J2.1 (S), J2.5 (TN), J3.1 (S), R1.2, R2.2, R5.2, SW1.6 (B), U1.4 (V-)
IN: FXC1.1, FXR22.2, R1.1, SW1.3 (A), SW1.7 (C)
unnamed: D1.1 (K), R3.1
unnamed: FXC1.2, FXR1.1
unnamed: FXC2.1, FXQ1.1 (E), FXR3.2
unnamed: FXC2.2, FXR5.2, U1.3 (+)
unnamed: FXC3.1, FXR4.1
unnamed: FXC3.2, FXC4.1, FXD1.1 (K), FXD2.2 (A), FXR6.2, U1.2 (-)
unnamed: FXC4.2, FXD1.2 (A), FXD2.1 (K), FXR7.2, RV1.2, RV1.3, U1.1
unnamed: FXC5.2, FXR7.1, FXR9.2, RV2.1, U1.5 (+)
unnamed: FXC6.1, RV2.2
unnamed: FXC6.2, FXR8.2
unnamed: FXC7.1, FXR10.1, U1.7
unnamed: FXC7.2, FXR11.2
unnamed: FXC8.1, FXR12.2, Q1.3 (B)
unnamed: FXC8.2, RV3.2
unnamed: FXC9.1, FXR13.1
unnamed: FXQ1.3 (B), FXR1.2, FXR2.2
unnamed: FXR6.1, RV1.1
unnamed: FXR10.2, RV2.3, U1.6 (-)
unnamed: FXR11.1, RV3.3
unnamed: FXR13.2, FXR14.2, Q1.1 (E)
unnamed: J2.2 (T), SW1.4 (B)
unnamed: J3.2 (T), SW1.5 (B)
unnamed: R3.2, SW1.9 (C)
unnamed: SW1.1 (A), SW1.2 (A)
OUT: FXC9.2, FXR15.2, R2.1, SW1.8 (C)
